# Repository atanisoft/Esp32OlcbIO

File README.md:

# ESP32 OpenLCB IO Board

The ESP32 OpenLCB IO Board is a basic OpenLCB (LCC) node offering 14 input/output
capable pins, and two that are input only. Additionally all IO pins are exposed
through two 13 pin headers which allows for extending the functionality of 
the base board using a daughter board approach.

## Powering the ESP32 OpenLCB IO Board

The ESP32 OpenLCB IO Board can be powered from an external power supply (12V) on
J5 connector, or using the OpenLCB (LCC) Bus power on RJ45. To enable powering
from the external supply, bridge pins 1 and 2 on JP1. To power from the OpenLCB
(LCC) Bus, bridge pins 2 and 3. Note that when using the USB connector on the
ESP32 module JP1 should not have any pins bridged.

### OpenLCB (LCC) Power requirements

The ESP32 OpenLCB IO Board will draw around 100mA from the OpenLCB (LCC) Bus when
the PWR_POS pin provides 15VDC. If the PWR_POS pin provides less, the node may
draw more current from the bus.

### External Power requirements

The external power supply should be rated for at least 12VDC 500mA to ensure
sufficient current is available for the node to operate as intended.

### Node Brownout detection

If the ESP32 detects a brownout condition it will attempt to produce the
well-known event `01.00.00.00.00.00.FF.F1` soon after startup. This delivery
is not guaranteed.

## Pin Mapping

By default almost all pins are exposed for general IO usage by the node,
however a few pins have specialized usage as part of the screw terminals or
expansion headers.

| GPIO Pin | Usage | Notes |
| -------- | ----- | ----- |
| 0 | IO4 | has pull-up resistor |
| 1 | UART0 TX | not exposed |
| 2 | IO5 | has pull-down resistor |
| 3 | UART0 RX | not exposed |
| 4 | CAN RX | has pull-down resistor |
| 5 | CAN TX | has pull-up resistor |
| 6-11 | NOT AVAILABLE | connected to on chip flash |
| 12 | IO7 | has pull-down resistor |
| 13 | IO8 | |
| 14 | IO16 | |
| 15 | IO6 | has pull-up resistor |
| 16 | IO3 | |
| 17 | IO2 | |
| 18 | IO1 | |
| 19 | I2C - SDA | |
| 20 | NOT AVAILABLE | NOT AVAILABLE |
| 21 | I2C - SCL | |
| 22 | Node Activity LED | active low |
| 23 | WiFi Active LED | active low |
| 24 | NOT AVAILABLE | NOT AVAILABLE |
| 25 | IO13 | |
| 26 | IO14 | |
| 27 | IO15 | |
| 28-31 | NOT AVAILABLE | NOT AVAILABLE |
| 32 | IO11 | |
| 33 | IO12 | |
| 34 | IO9 | INPUT ONLY, has pull-up resistor |
| 35 | IO10 | INPUT ONLY |
| 36 (SVP) | User button | INPUT ONLY, has pull-up resistor |
| 37 | NOT AVAILABLE | NOT AVAILABLE |
| 38 | NOT AVAILABLE | NOT AVAILABLE |
| 39 (SVP) | Factory Reset button | INPUT ONLY, has pull-up resistor |

### Input only pins

The four pins marked as INPUT ONLY in the table above have a 10k pull-up to
3v3 and a 100nF capacitor for debounce.

### IO4, IO5, IO6, IO7 Usage Note

IO4 and IO6 typically have a pull-up resistor. IO5 and IO7 typically have a
pull-down resistor that can not be disabled. Keep this in mind as this may
require adjustments to usage patterns.

## Base ESP32 OpenLCB IO PCB

The ESP32 OpenLCB IO Board PCB can be found under the pcb directory and is
provided as both KiCad files and generated Gerber files.

**NOTE:** U6 (CAN Transceiver) BOM line item references IFX1050GVIOXUMA1 which is no longer in production, please use one of the following instead:

* TJA1057GT/3J
* TCAN1051
* MCP2562

### PCBWay project

The ESP32 OpenLCB IO PCB has been shared via PCBWay [here](https://www.pcbway.com/project/shareproject/ESP32_OpenLCB__LCC__IO_PCB.html).

### Mouser BOM

The ESP32 OpenLCB IO Board components have been entered on Mouser for easy ordering
via the following shared carts:
- [single PCB](https://www.mouser.com/ProjectManager/ProjectDetail.aspx?AccessID=6d57d6cf6a)
- [five PCBs](https://www.mouser.com/ProjectManager/ProjectDetail.aspx?AccessID=a15be25217)

Ordering in larger quantities can decrease the per-PCB cost considerably. In
the case of resistors and capacitors it is recommended to order 100 of each
as they are tiny and easily lost. Other parts can often be substituted as long
as they have the same footprint and pinout. The pin headers will need to be cut
to length in both of the carts above, in the case of the five PCBs option there
should be enough to populate all five PCBs for the ESP32 *AND* the extension
board (when available).

#### Optional parts

The following parts are optional depending on board usage:

| Part | Mouser # | Notes |
| ---- | -------- | ----- |
| J2, J4 | 571-6-534237-1 | These are only needed for attaching an extension daughter board. |
| J5 | 523-NY0210800000G | This is only required if using an external power supply. |

#### Alternative part numbers

The following parts have compatible alternatives:

| Part | Default Mouser # | Alternative Mouser # | Notes |
| ---- | ---------------- | -------------------- | ----- |
| J2, J4 | 571-6-534237-1 | 992-13FX1-254MM, 485-598, 485-4158, 485-4156, 485-4159, 485-4157, 485-4155, 485-4160 | Parts 485-XXXX will need to be cut to the correct length. |
| J6, J7 | 571-5569284-1 | 534-949 or 493-HCJV1-812UK |

## Extending the base board

The ESP32 OpenLCB IO Board can be extended by using the pcb-ext daughter board
files as a basis for creating a compatible extension PCB. This PCB sits on top
of the base board.

### 16 Channel PWM generator expansion

The first expansion board is the 16 Channel PWM generator board, this is usable
for Servo or LED control. This expansion board utilizes a PCA9685 to generate
16 PWM signals which are routed to a three pin header (GND, 5V and PWM) for
each output.

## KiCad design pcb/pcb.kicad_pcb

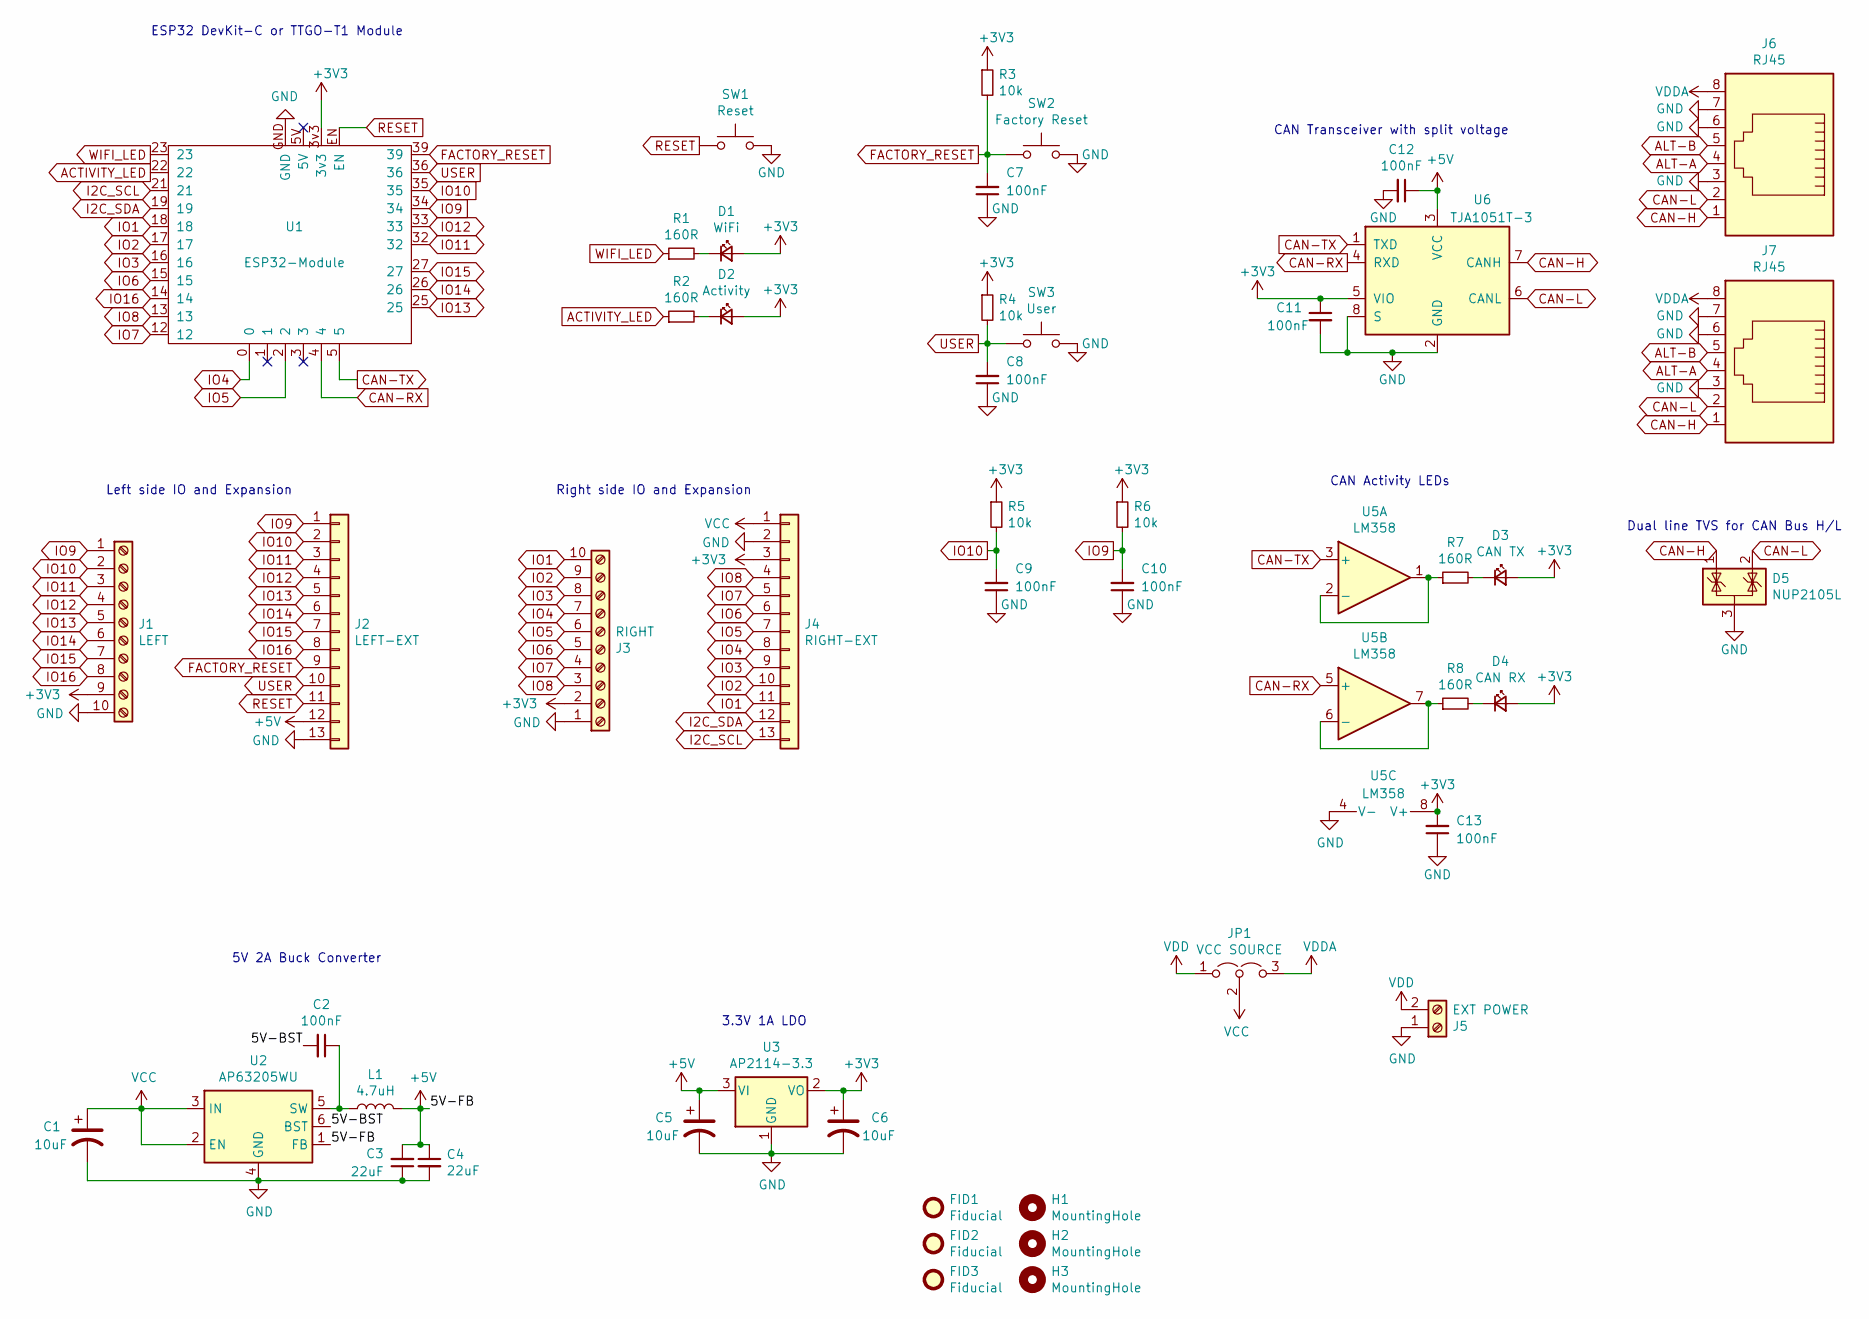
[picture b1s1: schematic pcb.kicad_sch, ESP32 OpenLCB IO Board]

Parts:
C1, C5, C6: 10uF; CP_Elec_5x5.3; Mouser 710-865230542002
C2, C7, C8, C9, C10, C11, C12, C13: 100nF; C_0603_1608Metric; Mouser 710-885012206020
C3, C4: 22uF; C_0603_1608Metric; Mouser 603-CC0603MRX6S5B226
D1: WiFi; LED_0603_1608Metric; Mouser 710-150060VS55040
D2: Activity; LED_0603_1608Metric; Mouser 710-150060AS75000
D3: CAN TX; LED_0603_1608Metric; Mouser 710-150060YS75000
D4: CAN RX; LED_0603_1608Metric; Mouser 710-150060AS75000
D5: NUP2105L; SOT-23; Mouser 863-SZNUP2105LT3G
FID1, FID2, FID3: Fiducial; Fiducial_0.5mm_Mask1mm
H1, H2, H3: MountingHole; MountingHole_2.7mm_M2.5
J1: LEFT; TerminalBlock_Phoenix_PT-1,5-10-3.5-H_1x10_P3.50mm_Horizont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; Mouser 649-220327-C101B01LF
J2: LEFT-EXT; PinSocket_1x13_P2.54mm_Vertical; Mouser 571-6-534237-1 or 992-13FX1-254MM
J3: RIGHT; TerminalBlock_Phoenix_PT-1,5-10-3.5-H_1x10_P3.50mm_Horizont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; Mouser 649-220327-C101B01LF
J4: RIGHT-EXT; PinSocket_1x13_P2.54mm_Vertical; Mouser 571-6-534237-1 or 992-13FX1-254MM
J5: EXT POWER; TerminalBlock_Phoenix_PT-1,5-2-3.5-H_1x02_P3.50mm_Horizontal; Mouser 651-1984617
J6, J7: RJ45; RJ45_OST_PJ012-8P8CX_Vertical; Mouser 571-5569284-1 or 534-949 or 493-HCJV1-8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
JP1: VCC SOURCE; PinHeader_1x03_P2.54mm_Vertical; Mouser 538-22-28-9034
L1: 4.7uH; L_7.3x7.3_H4.5; Mouser 81-B1047AS-4R7NP3
R1, R2, R7, R8: 160R; R_0603_1608Metric; Mouser 603-AC0603JR-07160RL
R3, R4, R5, R6: 10k; R_0603_1608Metric; Mouser 71-CRCW06030000Z0EAC
SW1: Reset; SW_SPST_EVQPE1; Mouser 667-EVQ-PE104K
SW2: Factory Reset; SW_SPST_EVQPE1; Mouser 667-EVQ-PE104K
SW3: User; SW_SPST_EVQPE1; Mouser 667-EVQ-PE104K
U1: ESP32-Module; TTGO-T1-DEVKIT-C
U2: AP63205WU; TSOT-23-6; Mouser 621-AP63205WU-7
U3: AP2114-3.3; SOT-223-3_TabPin2; Mouser 621-AP2114H-3.3TRG1
U5: LM358; SOIC-8_3.9x4.9mm_P1.27mm; Mouser 595-LM358BIDR
U6: TJA1051T-3; SOIC-8_3.9x4.9mm_P1.27mm; Mouser 726-IFX1050GVIOXUMA1

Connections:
+3V3: C6.1, C11.1, C13.2, D1.2 (A), D2.2 (A), D3.2 (A), D4.2 (A), J1.9, J3.2, J4.3, R3.1, R4.1, R5.1, R6.1, U1.3v3, U3.2 (VO), U5.8 (V+), U6.5 (VIO)
+5V: C3.2, C4.1, C5.1, C12.1, J2.12, L1.2, U2.1 (FB), U3.3 (VI), U6.3 (VCC)
/5V-BST: C2.2, U2.6 (BST)
ACTIVITY_LED: R2.1, U1.22
ALT-A: J6.4, J7.4
ALT-B: J6.5, J7.5
CAN-H: D5.1 (K), J6.1, J7.1, U6.7 (CANH)
CAN-L: D5.2 (K), J6.2, J7.2, U6.6 (CANL)
CAN-RX: U1.4, U5.5 (+), U6.4 (RXD)
CAN-TX: U1.5, U5.3 (+), U6.1 (TXD)
FACTORY_RESET: C7.2, J2.9, R3.2, SW2.1, U1.39
GND: C1.2, C3.1, C4.2, C5.2, C6.2, C7.1, C8.1, C9.1, C10.1, C11.2, C12.2, C13.1, D5.3 (A), J1.10, J2.13, J3.1, J4.2, J5.1, J6.3, J6.6, J6.7, J7.3, J7.6, J7.7, SW1.2, SW2.2, SW3.2, U1.GND, U2.4 (GND), U3.1 (GND), U5.4 (V-), U6.2 (GND), U6.8 (S)
I2C_SCL: J4.13, U1.21
I2C_SDA: J4.12, U1.19
IO1: J3.10, J4.11, U1.18
IO2: J3.9, J4.10, U1.17
IO3: J3.8, J4.9, U1.16
IO4: J3.7, J4.8, U1.0
IO5: J3.6, J4.7, U1.2
IO6: J3.5, J4.6, U1.15
IO7: J3.4, J4.5, U1.12
IO8: J3.3, J4.4, U1.13
IO9: C10.2, J1.1, J2.1, R6.2, U1.34
IO10: C9.2, J1.2, J2.2, R5.2, U1.35
IO11: J1.3, J2.3, U1.32
IO12: J1.4, J2.4, U1.33
IO13: J1.5, J2.5, U1.25
IO14: J1.6, J2.6, U1.26
IO15: J1.7, J2.7, U1.27
IO16: J1.8, J2.8, U1.14
unnamed: C2.1, L1.1, U2.5 (SW)
unnamed: D1.1 (K), R1.2
unnamed: D2.1 (K), R2.2
unnamed: D3.1 (K), R7.2
unnamed: D4.1 (K), R8.2
unnamed: R7.1, U5.1, U5.2 (-)
unnamed: R8.1, U5.6 (-), U5.7
RESET: J2.11, SW1.1, U1.EN
USER: C8.2, J2.10, R4.2, SW3.1, U1.36
VCC: C1.1, J4.1, JP1.2 (C), U2.2 (EN), U2.3 (IN)
VDD: J5.2, JP1.1 (A)
VDDA: J6.8, J7.8, JP1.3 (B)
WIFI_LED: R1.1, U1.23

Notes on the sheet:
Right side IO and Expansion
5V 2A Buck Converter
Left side IO and Expansion
3.3V 1A LDO
ESP32 DevKit-C or TTGO-T1 Module
CAN Transceiver with split voltage
CAN Activity LEDs
Dual line TVS for CAN Bus H/L

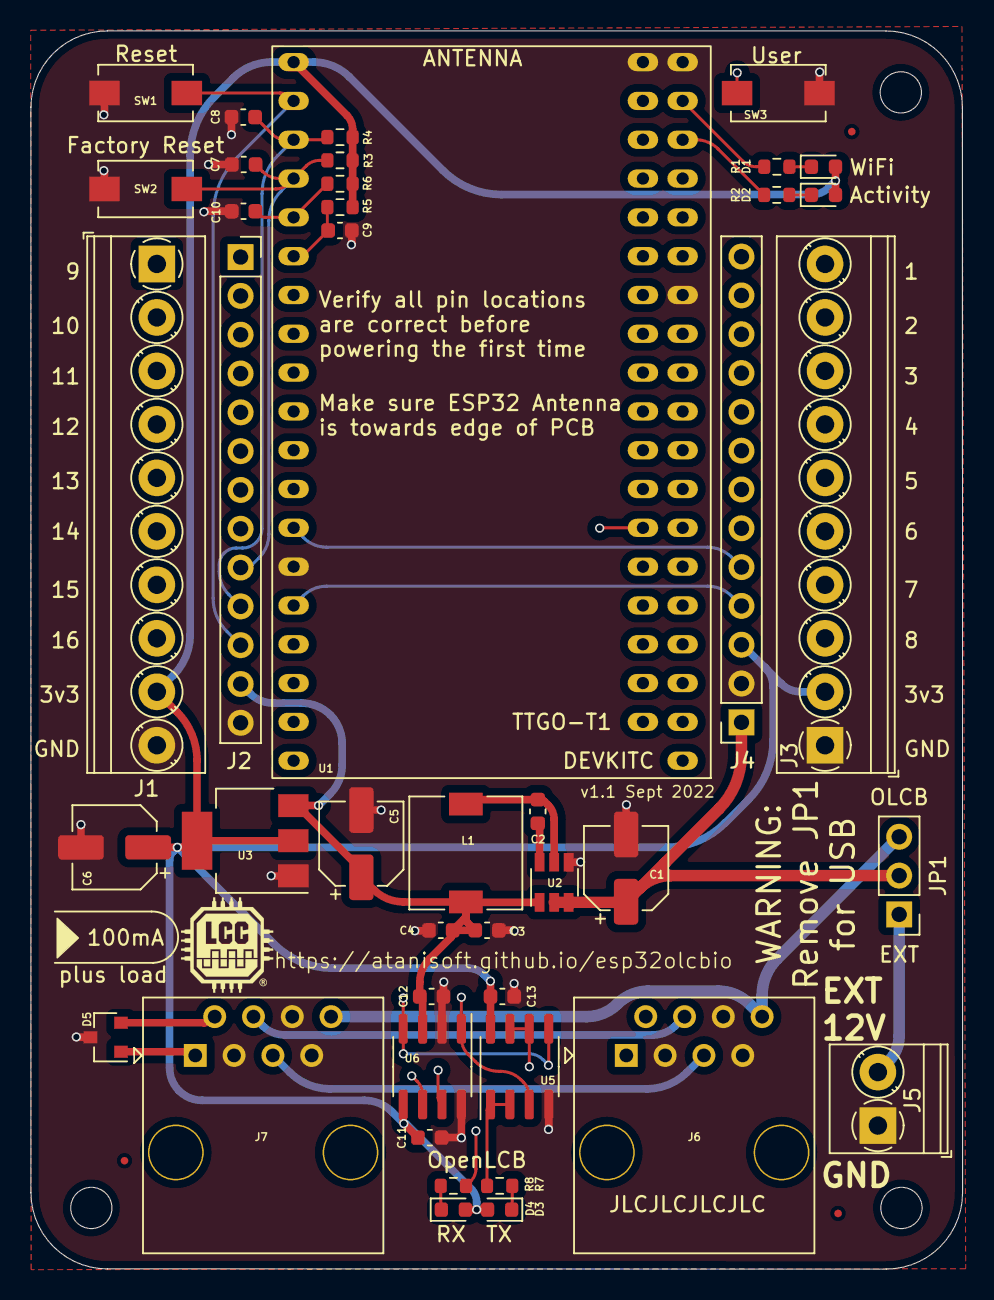
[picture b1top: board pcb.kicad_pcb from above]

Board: 4 copper layers, 61.0 x 81.0 mm, 49 parts (0 on the bottom side), 43 nets.

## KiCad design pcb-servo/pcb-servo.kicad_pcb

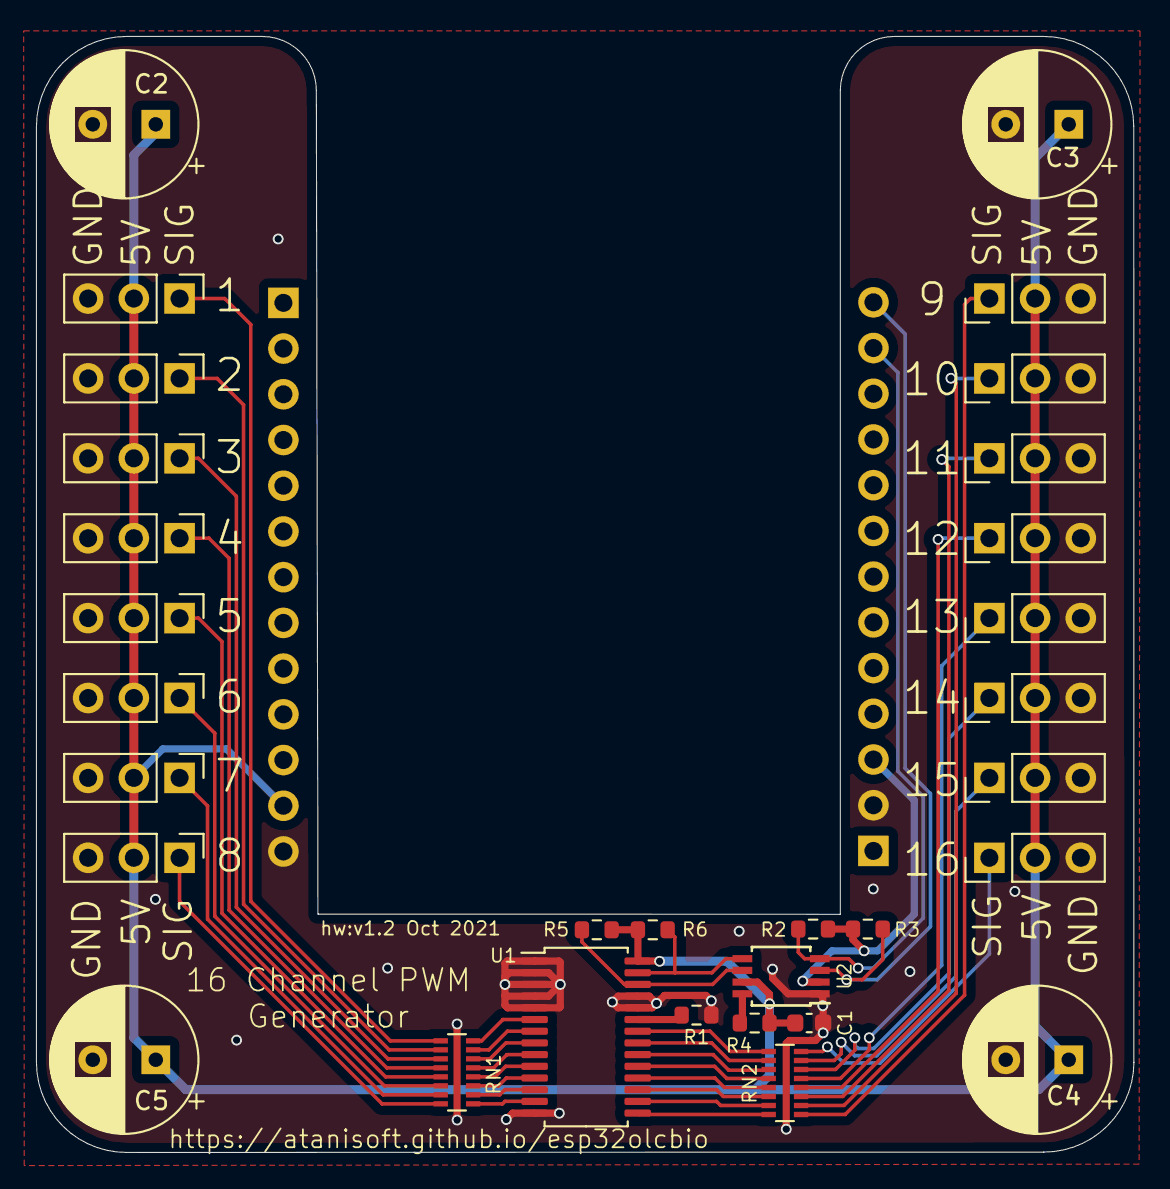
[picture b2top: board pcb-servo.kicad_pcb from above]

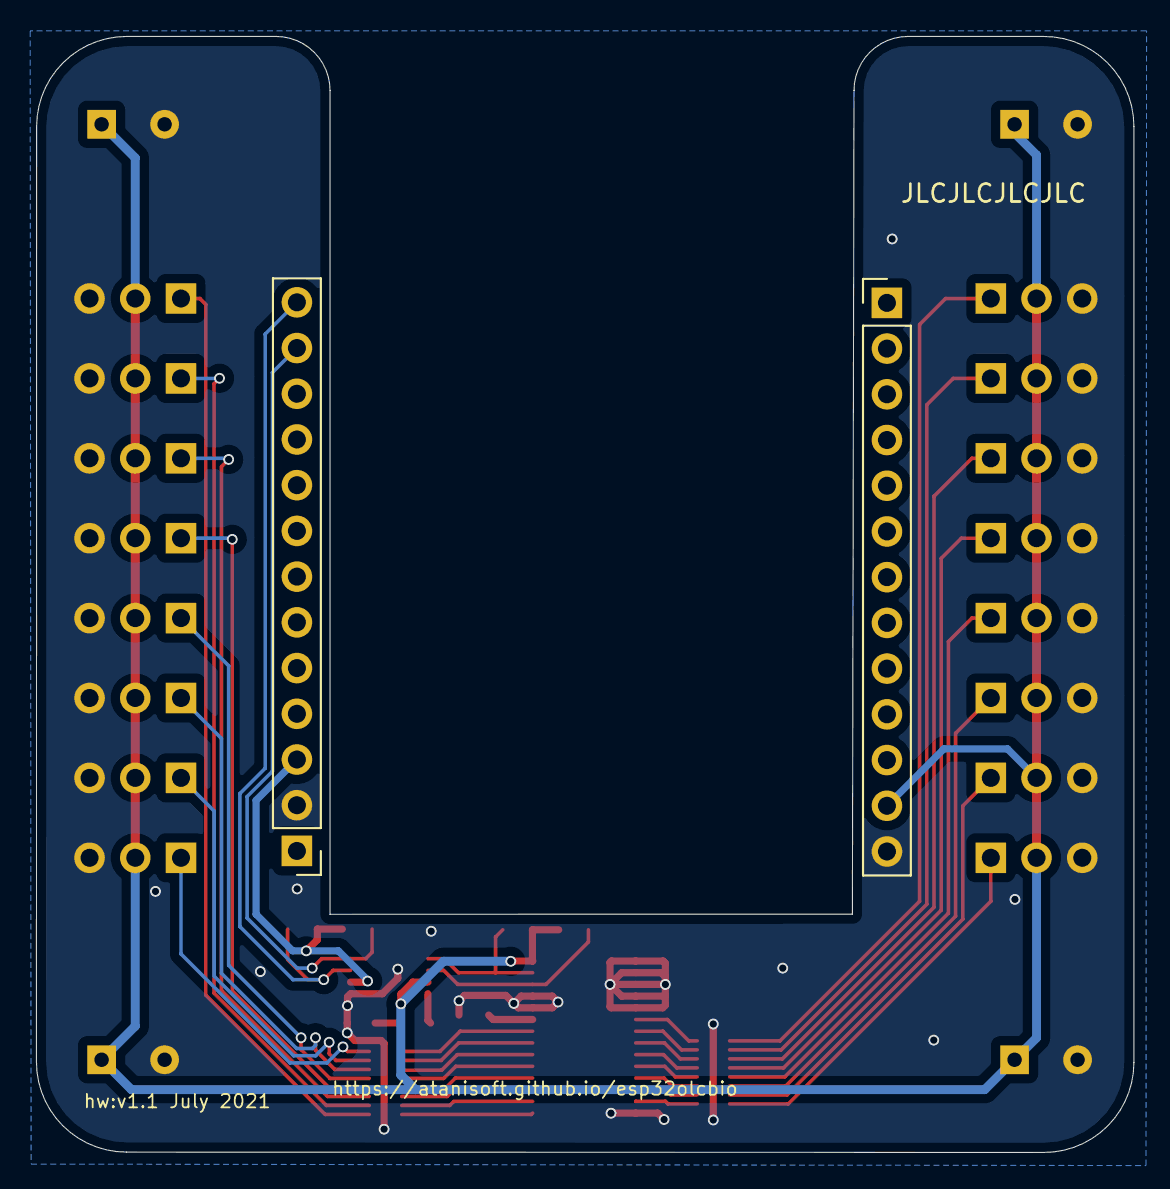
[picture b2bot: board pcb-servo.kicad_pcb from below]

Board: 2 copper layers, 61.0 x 62.0 mm, 33 parts (2 on the bottom side), 41 nets.

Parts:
C1: 10uF; C_0603_1608Metric
C2, C3, C4, C5: DNP; CP_Radial_D8.0mm_P3.50mm
J1, J2, J3, J4, J5, J6, J7, J8, J9, J10, J11, J12, J13, J14, J15, J16: PWM; PinHeader_1x03_P2.54mm_Vertical
J17: LEFT-EXT; PinHeader_1x13_P2.54mm_Vertical
J18: RIGHT-EXT; PinHeader_1x13_P2.54mm_Vertical
R1: 10K; R_0603_1608Metric
R2, R3: 2K4; R_0603_1608Metric
R4: 200K; R_0603_1608Metric
R5, R6: 4k7; R_0603_1608Metric
RN1, RN2: 220R; R_Array_Convex_8x0602
U1: PCA9685PW; TSSOP-28_4.4x9.7mm_P0.65mm
U2: PCA9306; TSSOP-8_3x3mm_P0.65mm

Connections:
5V_I2C_SCL: R5.2, U1.26, U2.6
5V_I2C_SDA: R6.2, U1.27, U2.5
+3V3: J18.3, R2.1, R3.1, U2.2
+5V: C1.1, C2.1, C3.1, C4.1, C5.1, J1.2, J2.2, J3.2, J4.2, J5.2, J6.2, J7.2, J8.2, J9.2, J10.2, J11.2, J12.2, J13.2, J14.2, J15.2, J16.2, J17.12, R4.1, R5.1, R6.1, U1.28, U2.7
GND: C1.2, C2.2, C3.2, C4.2, C5.2, J1.3, J2.3, J3.3, J4.3, J5.3, J6.3, J7.3, J8.3, J9.3, J10.3, J11.3, J12.3, J13.3, J14.3, J15.3, J16.3, J17.13, J18.2, R1.2, U1.1, U1.2, U1.3, U1.4, U1.5, U1.14, U1.24, U1.25, U2.1
I2C_SCL: J18.13, R3.2, U2.3
I2C_SDA: J18.12, R2.2, U2.4
unnamed: R1.1, U1.23
unnamed: R4.2, U2.8
unnamed: RN1.9, U1.13
unnamed: RN1.10, U1.12
unnamed: RN1.11, U1.11
unnamed: RN1.12, U1.10
unnamed: RN1.13, U1.9
unnamed: RN1.14, U1.8
unnamed: RN1.15, U1.7
unnamed: RN1.16, U1.6
unnamed: RN2.1, U1.22
unnamed: RN2.2, U1.21
unnamed: RN2.3, U1.20
unnamed: RN2.4, U1.19
unnamed: RN2.5, U1.18
unnamed: RN2.6, U1.17
unnamed: RN2.7, U1.16
unnamed: RN2.8, U1.15
PWM-1: J1.1, RN1.1
PWM-2: J5.1, RN1.2
PWM-3: J9.1, RN1.3
PWM-4: J13.1, RN1.4
PWM-5: J2.1, RN1.5
PWM-6: J6.1, RN1.6
PWM-7: J10.1, RN1.7
PWM-8: J14.1, RN1.8
PWM-9: J3.1, RN2.9
PWM-10: J7.1, RN2.10
PWM-11: J11.1, RN2.11
PWM-12: J15.1, RN2.12
PWM-13: J4.1, RN2.13
PWM-14: J8.1, RN2.14
PWM-15: J12.1, RN2.15
PWM-16: J16.1, RN2.16

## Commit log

2020-11-16 :sparkles: Initial Commit
2020-11-16 rename submodule
2020-11-16 rename OpenMRNIDF -> OpenMRNLite
2020-11-17 :sparkles: Daughter board template
2020-11-17 :pencil: Initial pass at firmware and updates to the PCB.
2020-11-17 :pencil: Remove / from CDI group name
    This is a quick fix for the html interface to render the IO pins. A more complete fix will be to replace characters in the group name dynamically instead.
2020-11-17 :arrow_up: Sync HttpServer with WS fix
2020-11-17 :pencil: Add Mouser part numbers to BOM
2020-11-18 :pencil: Corrections to part numbers
    * C2 should have been 100nF and not 22uF
    * U3 needs to be able to provide 1A and not 600mA.
2020-11-18 :arrow_up: Sync HttpServer
2020-11-18 :pencil: Clarify the comment on can_rx_buffer_size
2020-11-18 :sparkles: Add "Reset Event IDs" to web interface :sparkles: Add "Refresh All" to web interface :pencil: Reformat event IDs so they show up as 00.00.00.00.00.00.00.00 instead of 0000000000000000. :pe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
2020-11-18 :arrow_up: Sync OpenMRN
2020-11-18 :pencil: default all pins to input
2020-11-19 :arrow_up: Sync OpenMRN.
    NOTE: This update requires enabling of `CONFIG_FREERTOS_SUPPORT_STATIC_ALLOCATION` which may not be needed in the future.
2020-11-19 :pencil: Update readme with alternative part numbers and extension board examples.
2020-11-19 :pencil: Update schematic with a few part alternatives
2020-11-19 :pencil: Add Fiducials to PCB :pencil: Adjust LED colors so they are not all red
2020-11-20 :sparkles: Add ability to set the SoftAP Channel via config. :pencil: Add validation of submodules presence. :pencil: Add die_with function to set blink pattern for NVS failure. :pencil: Add factory 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
2020-11-26 :tractor: Adjust sdkconfig.defaults to match sdkconfig section naming. :tractor: Extract WebSocket processing to it's own method. :pencil: Expose advanced config options.
2020-11-28 :arrow_down: Downgrade esp_littlefs to fix CDI fd issue
2020-11-28 :pencil: correct factory/user event handler
2020-11-28 :pencil: Increase accepted firmware size to ~1.5mb
2020-11-28 :sparkles: Add "test" button for events
2020-11-29 :pencil: Re-enable ability to reset node-id from web
2020-11-30 :sparkles: Basic bootloader support.
2020-12-01 :pencil: Split bootloader code for re-use.
    Additionally adds minimal firmware validation from the first segment received over CAN.
2020-12-02 :pencil: Correct BOM reference for 3v3 LDO
2020-12-05 :pencil: PCB BOM update
2020-12-05 :pencil: Switch to async TWAI
2020-12-05 :pencil: Enable GitHub Actions
2020-12-05 :pencil: Lower WND_DEFAULT since it prevents SoftAP from starting
2020-12-07 :arrow_up: Sync OpenMRN.
2020-12-07 :tractor: Move wifi config to CDI
2020-12-07 :pencil: Adjust Mouser BOM links.
2020-12-11 :pencil: Cleanup various hxx files for imports. :pencil: Improve build performance by pre-generating CDI and embedding it.
2020-12-12 :pencil: Disable LittleFS by default.
2020-12-14 :pencil: Drop WPA3 mapping
2020-12-14 pcb update for rename of repo
2020-12-27 :pencil: Add notes of ADC channels for IO pins.
2020-12-27 :pencil: Add WiFi-OFF build. :pencil: Remove NVS migration code (doesn't work).
2020-12-27 :pencil: Switch to build instead of app.
2020-12-27 :pencil: Fix artifact packaging name
2020-12-28 :ambulance: Fix SoftAP mode.
    For WPA (all variants) the minimum password length is eight characters, the default password being used previously was seven characters. With this change the SoftAP name and password will now be "esp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
    Added new behavior on the User button during startup. When only the User button is held during startup the WiFi debug diagnostics will be enabled and printed to the serial console.
2020-12-28 :arrow_up: Sync OpenMRNLite to pick up WiFi fix.
2020-12-28 :pencil: Fix path to readme.
2020-12-28 :pencil: Rename flashing readme
2020-12-28 :pencil: Test with IDF docker container
2020-12-28 :pencil: test 2
2020-12-28 :pencil: Test 3
2020-12-28 :pencil: test4
2020-12-28 :pencil: test 5
2020-12-28 :pencil: Fix path
2020-12-28 :pencil: Fix binary packaging
2020-12-28 :pencil: Switch to Docker based build
2021-02-01 :sparkles: PWM extension board
2021-02-01 :arrow_up: Update OpenMRN for I2C/PWM
2021-02-01 :tractor: WIP PWM generator
2021-02-01 :pencil: Add PWM to test builds
2021-02-03 :ambulance: Fix CDI parse failure due to stray node
2021-02-03 :sparkles: Add PWM to the web interface (if enabled)
2021-02-04 :pencil: Add URL encoding for string values
2021-02-05 :pencil: Migrate to Spectre.css
2021-02-07 :pencil: Adjust WS ping frequency
2021-02-07 :tractor: Replace PCA9685 PWM
2021-02-07 :pencil: Corrections to part numbers
2021-02-08 :pencil: Fix refresh all function reference
2021-02-20 :pencil: adjust PCB to use a cut out instead of solid panel
2021-02-20 :pencil: Remove deprecated warnings
2021-05-10 :sparkles: Adding very basic Arduino based firmware.
    This does not include the full functionality available with the ESP-IDF firmware but does provide a starting point for those that prefer an Arduino compatible firmware.
2021-07-22 Set theme jekyll-theme-dinky
2021-08-01 :tractor: Update with current PCB in testing.
2021-08-06 :tractor: Dependency refresh
2021-08-12 :tractor: Move web interface to use spectre.css
2021-10-16 :arrow_up: Bump to latest OpenMRNIDF
2021-10-16 :tractor: Dependency refresh (#6)
    * :tractor: Dependency refresh
    * :tractor: Move web interface to use spectre.css
    * :arrow_up: Bump to latest OpenMRNIDF
2022-09-13 Sync PWM changes
2022-09-13 bump build to IDF v4.4
2022-09-17 Bump dependencies
2022-09-17 refresh web interface for new servo config
2022-09-17 Fix https://github.com/atanisoft/Esp32OlcbIO/issues/8
2022-09-17 PCB updates for KiCad6
2022-09-17 IO PCB v1.1
    Spaced out RJ45 jacks to provide easier access to USB connector.
    Fixes: https://github.com/atanisoft/Esp32OlcbIO/issues/3
2022-09-17 drop old project files
2022-09-29 Adding one additional GND via to v1.1 PCB, add position file.
2022-11-25 Migrate to IDF component manager
2022-11-25 PCA9685 support (#9)
    * Sync PWM changes
    * bump build to IDF v4.4
    * Bump dependencies
    * refresh web interface for new servo config
    * Fix https://github.com/atanisoft/Esp32OlcbIO/issues/8
    * PCB updates for KiCad6
2022-11-26 Expand readme details for building and add automatic node ID support
2023-03-03 Removing automatic node assignment and use only pre-defined node i
2023-12-18 Update README.md
    Add references to alternative CAN transceivers
2023-12-23 Correct build instructions and dependencies
    The code will only build with ESP-IDF v5.1.x (or newer). It has not been tested with ESP-IDF v5.2 or master at this time.
    Fixes https://github.com/atanisoft/Esp32OlcbIO/issues/11
